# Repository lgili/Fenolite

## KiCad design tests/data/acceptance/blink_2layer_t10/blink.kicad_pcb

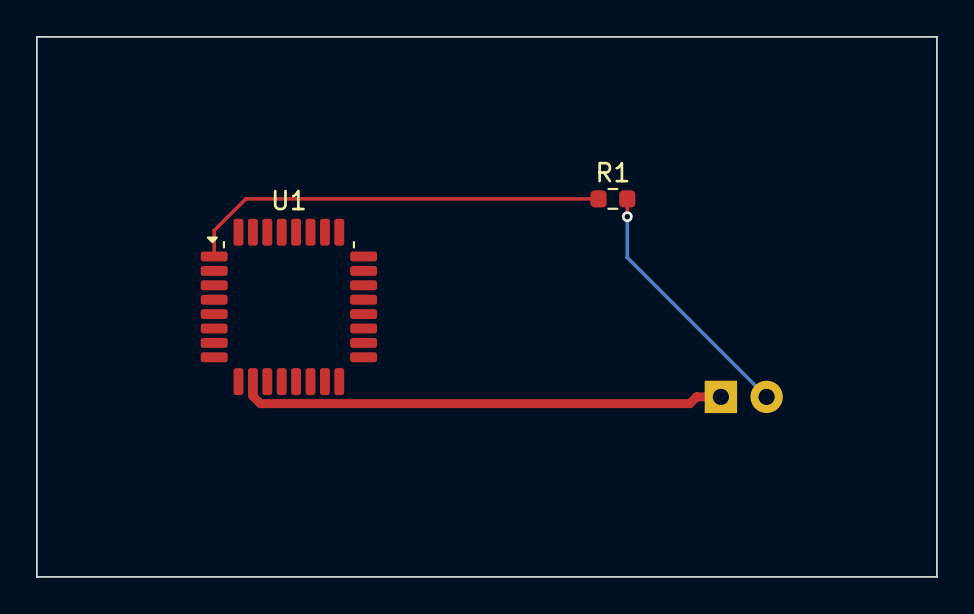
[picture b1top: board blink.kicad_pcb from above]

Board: 2 copper layers, 50.0 x 30.0 mm, 3 parts (1 on the bottom side), 3 nets.

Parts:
D1: LED; Mini_LED_THT_3mm
R1: 330; Mini_R_0603
U1: MCU; Mini_QFP-32_7x7mm_P0.8mm

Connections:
GND: D1.1, U1.10
LED_A: D1.2, R1.2
LED_DRV: R1.1, U1.1

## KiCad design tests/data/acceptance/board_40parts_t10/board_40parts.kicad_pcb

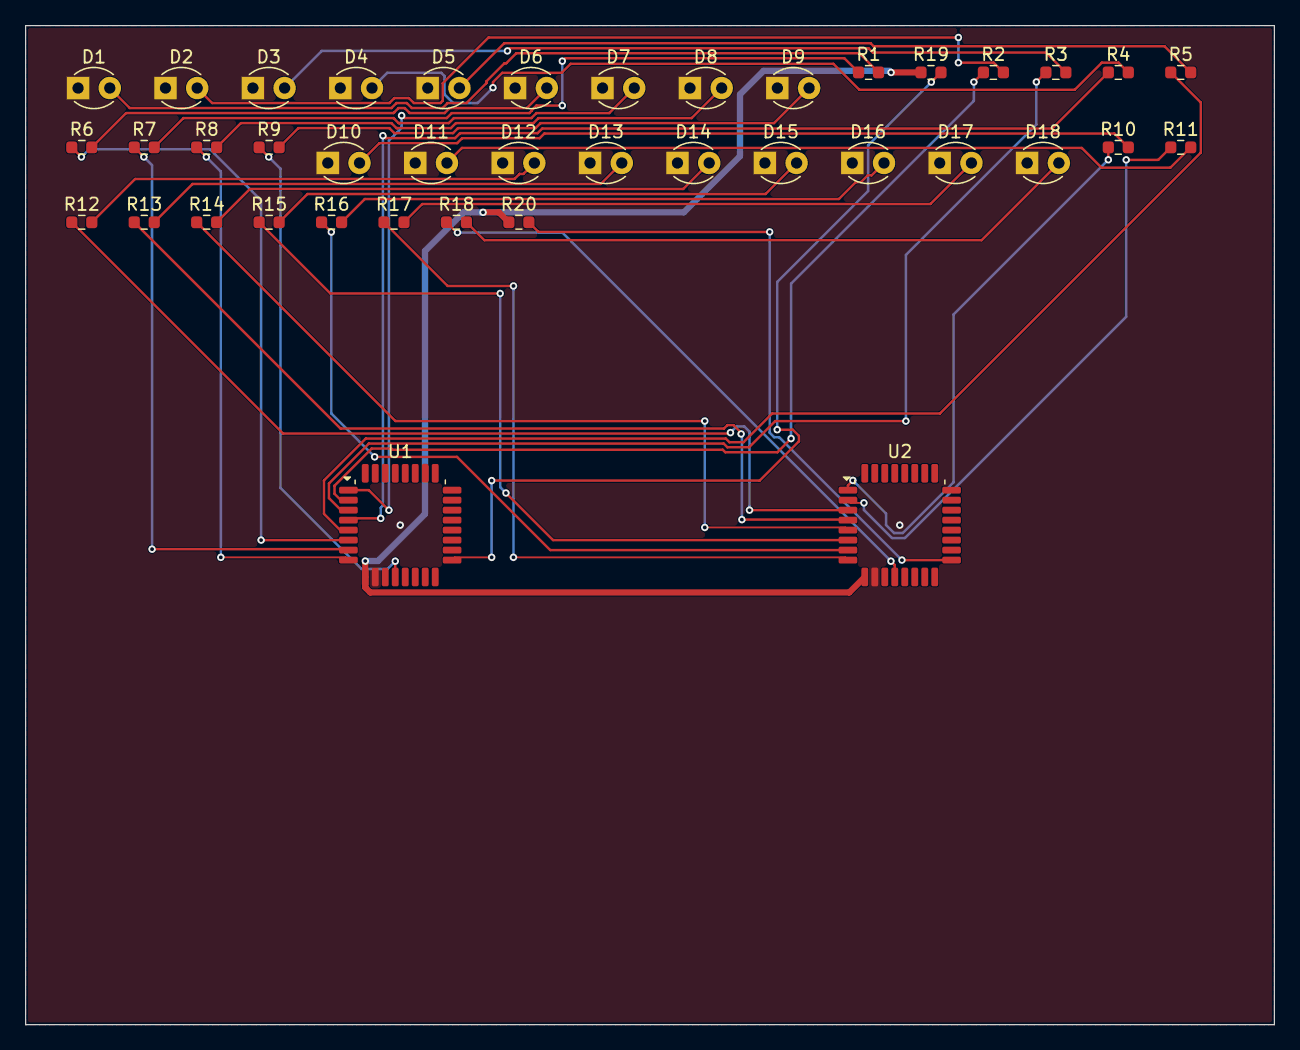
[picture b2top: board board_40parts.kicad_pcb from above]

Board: 2 copper layers, 100.0 x 80.0 mm, 40 parts (0 on the bottom side), 40 nets.

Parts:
D1, D2, D3, D4, D5, D6, D7, D8, D9, D10, D11, D12, D13, D14, D15, D16, D17, D18: LED; Mini_LED_THT_3mm
R1, R2, R3, R4, R5, R6, R7, R8, R9, R10, R11, R12, R13, R14, R15, R16, R17, R18: 330; Mini_R_0603
R19, R20: 10k; Mini_R_0603
U1, U2: MCU; Mini_QFP-32_7x7mm_P0.8mm

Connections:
DRV1: R1.1, U1.1
DRV2: R2.1, U1.2
DRV3: R3.1, U1.3
DRV4: R4.1, U1.4
DRV5: R5.1, U1.5
DRV6: R6.1, U1.6
DRV7: R7.1, U1.7
DRV8: R8.1, U1.8
DRV9: R9.1, U1.12
DRV10: R10.1, U2.1
DRV11: R11.1, U2.2
DRV12: R12.1, U2.3
DRV13: R13.1, U2.4
DRV14: R14.1, U2.5
DRV15: R15.1, U2.6
DRV16: R16.1, U2.7
DRV17: R17.1, U2.8
DRV18: R18.1, U2.12
EN1: R19.2, U1.17
EN2: R20.2, U2.17
GND: D1.1, D2.1, D3.1, D4.1, D5.1, D6.1, D7.1, D8.1, D9.1, D10.1, D11.1, D12.1, D13.1, D14.1, D15.1, D16.1, D17.1, D18.1, U1.10, U2.10
LED1: D1.2, R1.2
LED2: D2.2, R2.2
LED3: D3.2, R3.2
LED4: D4.2, R4.2
LED5: D5.2, R5.2
LED6: D6.2, R6.2
LED7: D7.2, R7.2
LED8: D8.2, R8.2
LED9: D9.2, R9.2
LED10: D10.2, R10.2
LED11: D11.2, R11.2
LED12: D12.2, R12.2
LED13: D13.2, R13.2
LED14: D14.2, R14.2
LED15: D15.2, R15.2
LED16: D16.2, R16.2
LED17: D17.2, R17.2
LED18: D18.2, R18.2
VIN: R19.1, R20.1, U1.9, U2.9
